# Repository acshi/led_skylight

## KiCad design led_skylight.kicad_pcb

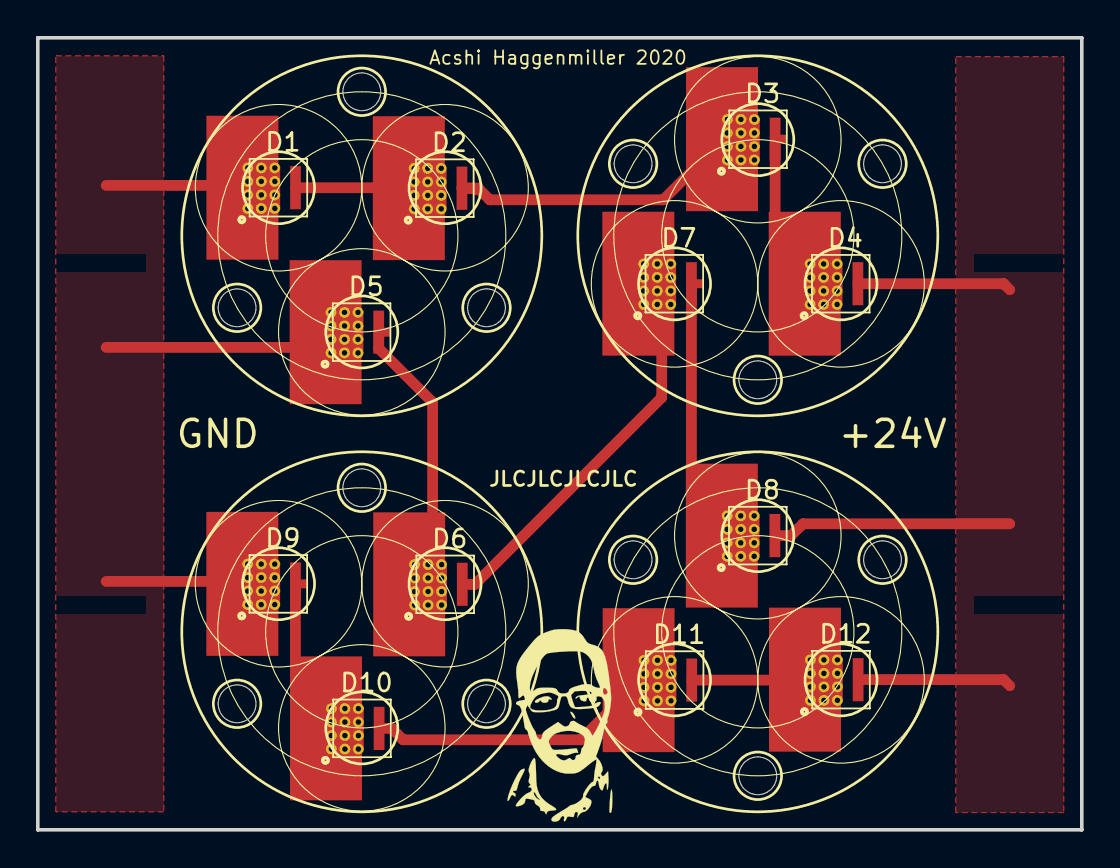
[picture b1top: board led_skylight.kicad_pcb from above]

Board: 2 copper layers, 58.0 x 44.0 mm, 12 parts (0 on the bottom side), 11 nets.

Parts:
D1, D2, D3, D4, D5, D6, D7, D8, D9, D10, D11, D12: JK3030AWT-P-U57; JK3030AWT-P

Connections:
+24V: D1.2, D5.2, D9.2
GND: D4.1, D8.1, D12.1
unnamed: D1.1, D2.2
unnamed: D2.1, D3.2
unnamed: D3.1, D4.2
unnamed: D5.1, D6.2
unnamed: D6.1, D7.2
unnamed: D7.1, D8.2
unnamed: D10.1, D11.2
unnamed: D9.1, D10.2
unnamed: D11.1, D12.2

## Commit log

2020-05-20 led skylight project; finalized pcbs; most of the mechanical design
